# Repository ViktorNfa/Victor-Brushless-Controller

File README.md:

# Victor Brushless Controller (VBC)

This repository contains the **firmware** and **KiCad hardware design files** for the **Victor Brushless Controller (VBC)**, a custom BLDC motor controller inspired by the [Dagor Brushless Controller](https://github.com/byDagor/Dagor-Brushless-Controller).

## Overview

VBC is a compact, ESP32-based brushless controller designed for use in robotic and actuator applications. It integrates key hardware components to support precise control of brushless motors with wired or wireless communication.

The controller supports three operation modes:
- **Position control**.
- **Velocity control**.
- **Torque control**.

In both voltage- and current-control modes. It is compatible with the [SimpleFOC](https://docs.simplefoc.com/) library and can be programmed using the Arduino IDE.

## Features

- ESP32-based microcontroller.
- Onboard 3-phase MOSFET driver and half-bridges.
- Integrated 14-bit magnetic encoder.
- Current sensing resistors.
- Onboard temperature sensor.
- Custom firmware tailored for SimpleFOC.
- KiCad schematics and PCB layout included.

## Hardware Specs

| Specification             | Value           |
|---------------------------|------------------|
| Board Dimensions          | ~44 x 44 mm      |
| Supply Voltage            | 5 – 24 V         |
| Peak RMS Current          | up to 40 A       |
| Magnetic Sensor Resolution| 14 bits          |
| Temperature Range         | -10°C to 120°C   |

> 🧪 Note: This is a **custom derivative project**, still under development. Use with caution and test thoroughly.

## Repository Structure

- `VBC-SW/` – Source code for the controller (Arduino + SimpleFOC).
- `VBC-HW/` – KiCad project files for PCB schematics and layout.
- `KiCad_libraries/` – Custom footprints & symbols needed for KiCad.

## Acknowledgements

Based on the fantastic work by [@byDagor](https://github.com/byDagor) and the [Dagor Brushless Controller](https://docs.dagor.dev/).

## License

To decide – see `...` file for details.

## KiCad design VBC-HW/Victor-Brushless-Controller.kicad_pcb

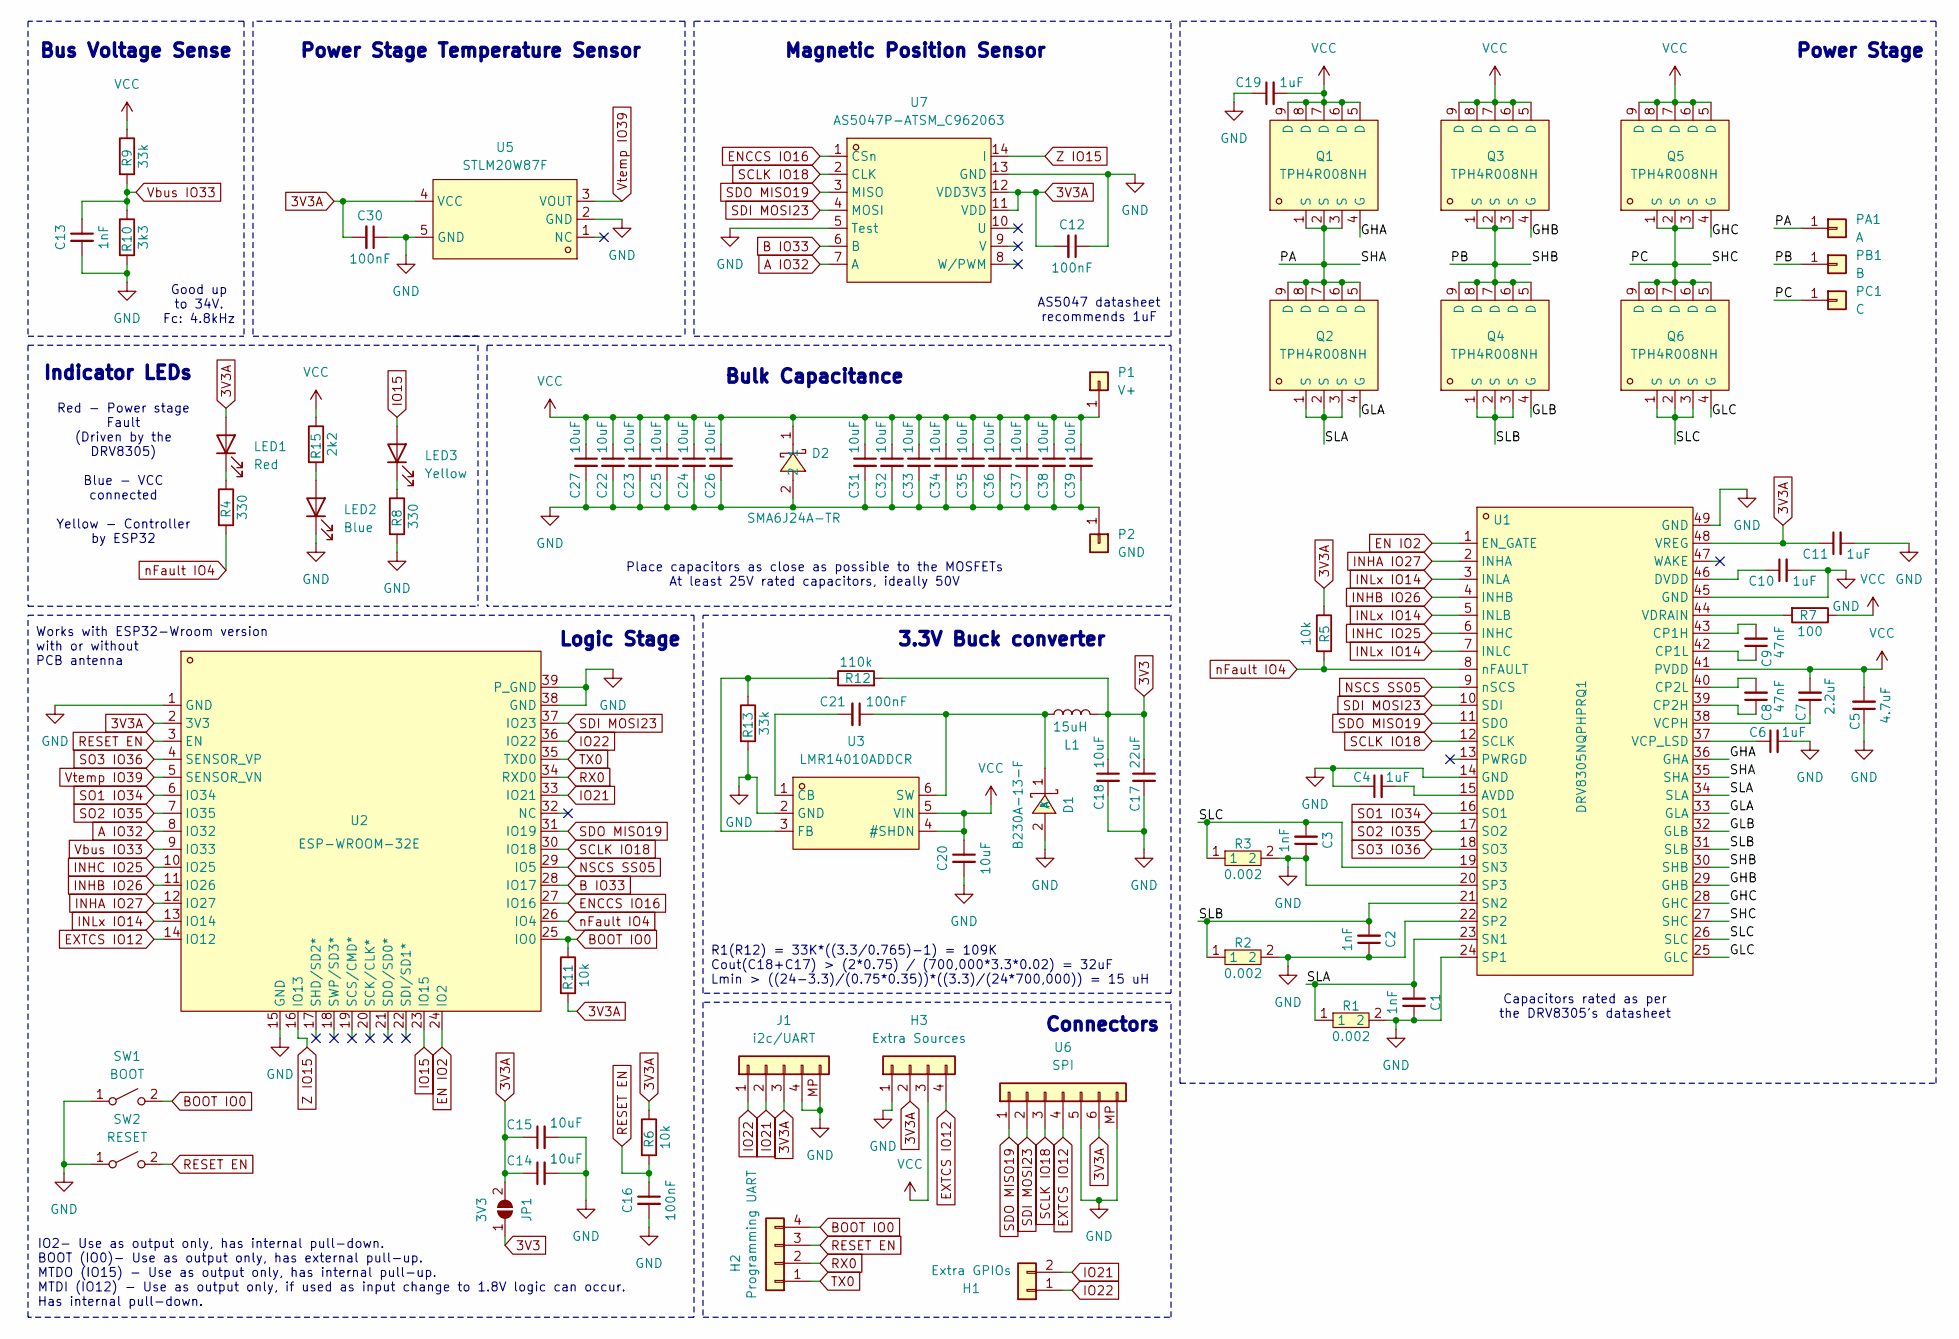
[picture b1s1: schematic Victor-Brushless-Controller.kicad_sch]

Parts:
C1, C2, C3, C13: 1nF; 0402B102K500NT
C4, C6, C10, C11: 1uF; CL05A105KA5NQNC
C5: 4.7uF; 1206B475K500NT
C7: 2.2uF; CL31B225KBHNNNE
C8: 47nF; CL21B473KCFNNNE
C9: 47nF; CL10B473KB8NNNC
C12, C16, C21, C30: 100nF; CL05B104KO5NNNC
C14: 10uF; CL05A106MQ5NUNC
C15: 10uF; CL05B104KO5NNNC
C17: 22uF; CL10A226MQ8NRNC
C18: 10uF; CL10A106MA8NRNC
C19: 1uF; CL10A105KB8NNNC
C20, C22, C23, C24, C25, C26, C27, C31, C32, C33, C34, C35, C36, C39: 10uF; GRM21BR61H106KE43L
C37, C38: 10uF; 1206X106M500NT
D1: B230A-13-F; LCSC Part C12889
D2: SMA6J24A-TR; SMA6J24A; LCSC Part C1975444
H1: Extra GPIOs; PinHeader_1x02_P2.54mm_Vertical
H2: Programming UART; PinHeader_1x04_P2.54mm_Vertical
H3: Extra Sources; PinHeader_1x04_P2.54mm_Vertical
J1: i2c/UART; JST_GH_BM04B-GHS-TBT_1x04-1MP_P1.25mm_Vertical
JP1: 3V3; SolderJumper-2_P1.3mm_Open_Pad1.0x1.5mm
L1: 15uH; PIS3D18P-150M-T
LED1: Red; KT-0603R
LED2: Blue; 19-217
LED3: Yellow; 19-213
P1: V+; Power_Connector
P2: GND; Power_Connector
PA1: A; BLDC_Connector
PB1: B; BLDC_Connector
PC1: C; BLDC_Connector
Q1, Q2, Q3, Q4, Q5, Q6: TPH4R008NH; TPH4R008NH,L1Q(M; LCSC Part C396039
R1, R2, R3: 0.002; CUM2512-24FR002; LCSC Part C323765
R4, R8: 330; 0402WGF3300TCE
R5, R6, R11: 10k; 0402WGF1002TCE
R7: 100; 0402WGF1000TCE
R9, R13: 33k; 0402WGF3302TCE
R10: 3k3; 0402WGF3301TCE
R12: 110k; RC0402FR-07110KL
R15: 2k2; 0402WGF2201TCE
SW1: BOOT; TS342A2P-WZ
SW2: RESET; TS342A2P-WZ
U1: DRV8305NQPHPRQ1; LCSC Part C701780
U2: ESP-WROOM-32E; LCSC Part C19949066
U3: LMR14010ADDCR; LCSC Part C388174
U5: STLM20W87F; LCSC Part C129796
U6: SPI; JST_GH_BM06B-GHS-TBT_1x06-1MP_P1.25mm_Vertical
U7: AS5047P-ATSM_C962063; AS5047P-ATSM; LCSC Part C962063

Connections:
3V3: C17.1, C18.1, JP1.1 (A), L1.2, R12.2
3V3A: C11.1, C12.2, C14.1, C15.1, C30.2, H3.2, J1.3, JP1.2 (B), LED1.2 (A), R5.1, R6.1, R11.2, U1.48 (VREG), U2.2 (3V3), U5.4 (VCC), U6.6, U7.11 (VDD), U7.12 (VDD3V3)
/GHA: Q1.4 (G), U1.36 (GHA)
/GHB: Q3.4 (G), U1.29 (GHB)
/GHC: Q5.4 (G), U1.28 (GHC)
/GLA: Q2.4 (G), U1.33 (GLA)
/GLB: Q4.4 (G), U1.32 (GLB)
/GLC: Q6.4 (G), U1.25 (GLC)
/PA: PA1.1, Q1.1 (S), Q1.2 (S), Q1.3 (S), Q2.5 (D), Q2.6 (D), Q2.7 (D), Q2.8 (D), Q2.9 (D), U1.35 (SHA)
/PB: PB1.1, Q3.1 (S), Q3.2 (S), Q3.3 (S), Q4.5 (D), Q4.6 (D), Q4.7 (D), Q4.8 (D), Q4.9 (D), U1.30 (SHB)
/PC: PC1.1, Q5.1 (S), Q5.2 (S), Q5.3 (S), Q6.5 (D), Q6.6 (D), Q6.7 (D), Q6.8 (D), Q6.9 (D), U1.27 (SHC)
/SLA: C1.2, Q2.1 (S), Q2.2 (S), Q2.3 (S), R1.1, U1.23 (SN1), U1.34 (SLA)
/SLB: C2.2, Q4.1 (S), Q4.2 (S), Q4.3 (S), R2.1, U1.21 (SN2), U1.31 (SLB)
/SLC: C3.2, Q6.1 (S), Q6.2 (S), Q6.3 (S), R3.1, U1.19 (SN3), U1.26 (SLC)
A IO32: U2.8 (IO32), U7.7 (A)
B IO33: U2.28 (IO17), U7.6 (B)
BOOT IO0: H2.4, R11.1, SW1.2 (B), U2.25 (IO0)
EN IO2: U1.1 (EN_GATE), U2.24 (IO2)
ENCCS IO16: U2.27 (IO16), U7.1 (CSn)
EXTCS IO12: H3.4, U2.14 (IO12), U6.4
GND: C1.1, C2.1, C3.1, C4.1, C5.1, C6.2, C10.2, C11.2, C12.1, C13.2, C14.2, C15.2, C16.2, C17.2, C18.2, C19.1, C20.2, C22.2, C23.2, C24.2, C25.2, C26.2, C27.2, C30.1, C31.2, C32.2, C33.2, C34.2, C35.2, C36.2, C37.2, C38.2, C39.2, D1.2 (A), D2.2, H3.1, J1.4, J1.MP, LED2.1 (K), P2.1, R1.2, R2.2, R3.2, R8.2, R10.2, R13.2, SW1.1 (A), SW2.1 (A), U1.14 (GND), U1.20 (SP3), U1.22 (SP2), U1.24 (SP1), U1.45 (GND), U1.49 (GND), U2.1 (GND), U2.15 (GND), U2.38 (GND), U2.39 (P_GND), U3.2 (GND), U5.2 (GND), U5.5 (GND), U6.5, U6.MP, U7.5 (Test), U7.13 (GND)
INHA IO27: U1.2 (INHA), U2.12 (IO27)
INHB IO26: U1.4 (INHB), U2.11 (IO26)
INHC IO25: U1.6 (INHC), U2.10 (IO25)
INLx IO14: U1.3 (INLA), U1.5 (INLB), U1.7 (INLC), U2.13 (IO14)
IO15: LED3.2 (A), U2.23 (IO15)
IO21: H1.2, J1.2, U2.33 (IO21)
IO22: H1.1, J1.1, U2.36 (IO22)
NSCS SS05: U1.9 (nSCS), U2.29 (IO5)
unnamed: C21.1, D1.1 (K), L1.1, U3.6 (SW)
unnamed: LED1.1 (K), R4.1
unnamed: LED2.2 (A), R15.2
unnamed: LED3.1 (K), R8.1
unnamed: C4.2, U1.15 (AVDD)
unnamed: C9.2, U1.43 (CP1H)
unnamed: C9.1, U1.42 (CP1L)
unnamed: C8.1, U1.39 (CP2H)
unnamed: C8.2, U1.40 (CP2L)
unnamed: C10.1, U1.46 (DVDD)
unnamed: C7.1, U1.38 (VCPH)
unnamed: C6.1, U1.37 (VCP_LSD)
unnamed: R7.2, U1.44 (VDRAIN)
unnamed: C21.2, U3.1 (CB)
unnamed: R12.1, R13.1, U3.3 (FB)
RESET EN: C16.1, H2.3, R6.2, SW2.2 (B), U2.3 (EN)
RX0: H2.2, U2.34 (RXD0)
SCLK IO18: U1.12 (SCLK), U2.30 (IO18), U6.3, U7.2 (CLK)
SDI MOSI23: U1.10 (SDI), U2.37 (IO23), U6.2, U7.4 (MOSI)
SDO MISO19: U1.11 (SDO), U2.31 (IO19), U6.1, U7.3 (MISO)
SO1 IO34: U1.16 (SO1), U2.6 (IO34)
SO2 IO35: U1.17 (SO2), U2.7 (IO35)
SO3 IO36: U1.18 (SO3), U2.4 (SENSOR_VP)
TX0: H2.1, U2.35 (TXD0)
VCC: C5.2, C7.2, C19.2, C20.1, C22.1, C23.1, C24.1, C25.1, C26.1, C27.1, C31.1, C32.1, C33.1, C34.1, C35.1, C36.1, C37.1, C38.1, C39.1, D2.1, H3.3, P1.1, Q1.5 (D), Q1.6 (D), Q1.7 (D), Q1.8 (D), Q1.9 (D), Q3.5 (D), Q3.6 (D), Q3.7 (D), Q3.8 (D), Q3.9 (D), Q5.5 (D), Q5.6 (D), Q5.7 (D), Q5.8 (D), Q5.9 (D), R7.1, R9.1, R15.1, U1.41 (PVDD), U3.4 (#SHDN), U3.5 (VIN)
Vbus IO33: C13.1, R9.2, R10.1, U2.9 (IO33)
Vtemp IO39: U2.5 (SENSOR_VN), U5.3 (VOUT)
Z IO15: U2.16 (IO13), U7.14 (I)
nFault IO4: R4.2, R5.2, U1.8 (nFAULT), U2.26 (IO4)

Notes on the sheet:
3.3V Buck converter
Red - Power stage Fault (Driven by the DRV8305) Blue - VCC connected Yellow - Controller by ESP32
Power Stage Temperature Sensor
Capacitors rated as per the DRV8305's datasheet
Indicator LEDs
Power Stage
AS5047 datasheet recommends 1uF
Place capacitors as close as possible to the MOSFETs At least 25V rated capacitors, ideally 50V
Works with ESP32-Wroom version with or without PCB antenna
Bus Voltage Sense
Good up to 34V. Fc: 4.8kHz
Bulk Capacitance
Connectors
Magnetic Position Sensor
R1(R12) = 33K*((3.3/0.765)-1) = 109K Cout(C18+C17) > (2*0.75) / (700,000*3.3*0.02) = 32uF Lmin > ((24-3.3)/(0.75*0.35))*((3.3)/(24*700,000)) = 15 uH
IO2- Use as output only, has internal pull-down. BOOT (IO0)- Use as output only, has external pull-up. MTDO (IO15) - Use as output only, has internal pull-up. MTDI (IO12) - Use as output only, if used as input change to 1.8V logic can occur. Has internal pull-down.
Logic Stage

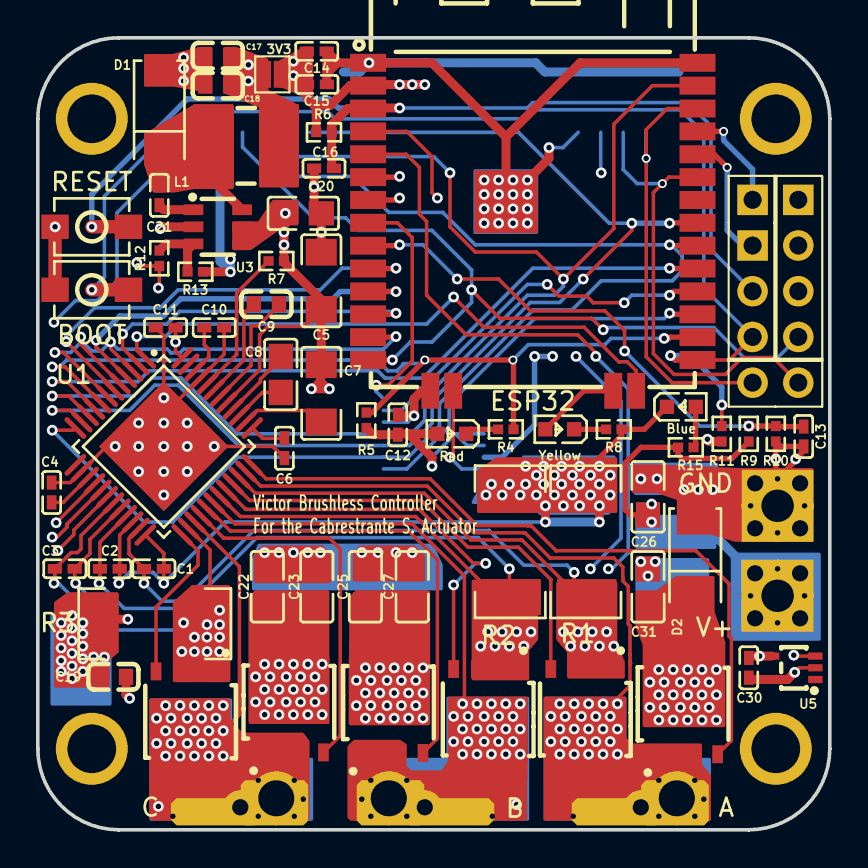
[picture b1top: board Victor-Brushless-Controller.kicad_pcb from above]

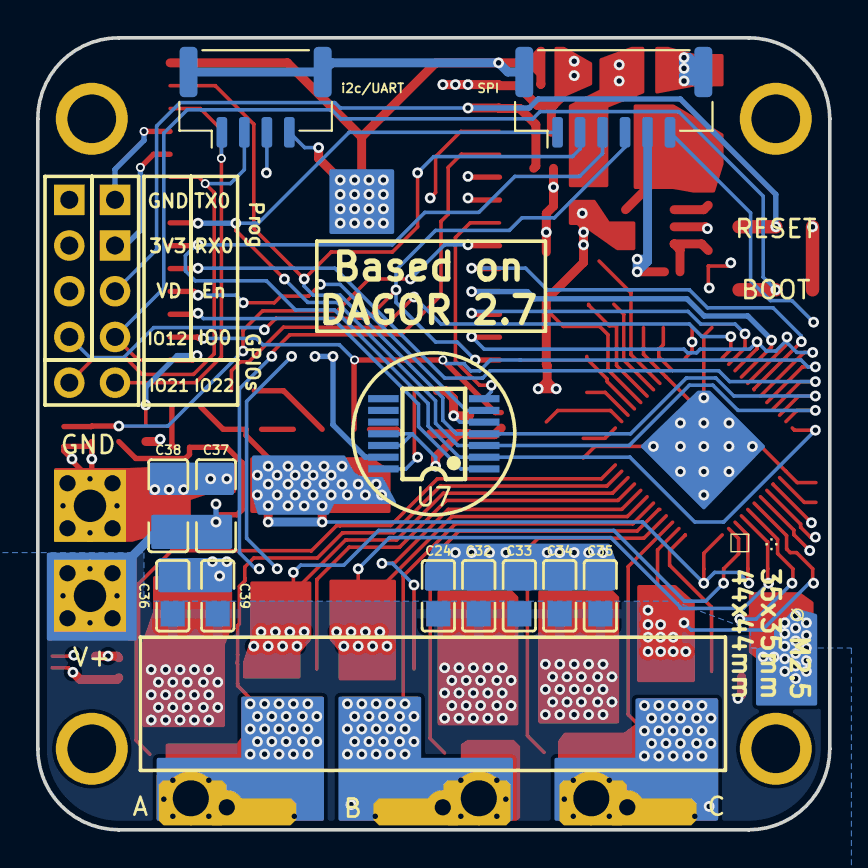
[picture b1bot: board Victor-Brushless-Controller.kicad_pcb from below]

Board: 4 copper layers, 44.0 x 44.0 mm, 81 parts (13 on the bottom side), 58 nets.

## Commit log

2025-03-29 Added KiCad libraries
2025-03-30 Added more micros and LCSC numbers
2025-04-01 Finished Power Stage schematic
2025-05-23 Added Kicad schematic magnetic, bus and temp
2025-05-26 Added buck converter
2025-05-26 Finished schematics connections
2025-05-26 Cleaned up schematic
2025-05-27 Started adding footprints
2025-06-02 Updated more components
2025-06-02 Fix errors
2025-06-03 Finish adding all components libraries
2025-06-03 Added footprints to project
2025-06-05 Added footprints to schematic
2025-06-12 Assigned external connectors
2025-06-12 Finished assigning and creating all footprints
2025-06-12 Ready to tetris
2025-06-14 Preliminary component placing
2025-06-14 PCB starting to take shape
2025-06-21 Updated PCB and code
2025-06-21 Added test codes for magnetic sensor
2025-06-21 Added dev branch of simpleFOC lib
2025-06-23 Adding new base tests
2025-06-24 Working with smaller GM3506 motor
2025-06-25 Updates connections in board
2025-06-25 Managed to get Getting started codes to work
2025-07-10 Added closed loop control
2025-07-11 Fix closed loop control
2025-07-12 Added init current sense
2025-07-14 Added current closed loop control test
2025-07-14 Fix current control
2025-07-16 Fixed basic current sense
2025-07-16 foc_current control now works
2025-07-16 Added infor about phase order
2025-07-18 Cleaned up the codes to work with Dagor version
2025-07-18 Working clean up of current control
2025-07-19 Final final cleanups
2025-07-19 Added tests for LA8308 motor
2025-07-20 Big motor working
2025-07-22 Tuned LA8308
2025-07-28 Added code for whacakapuncher
2025-07-29 Added temperature sensor
2025-07-30 Might be wrong, just saving for history
2025-07-30 Revert "Might be wrong, just saving for history"
    This reverts commit cdf17d161a2acca385215cf7318953e3e6c9fc40.
2025-07-30 Save scumming
2025-07-30 Final save for bar torque setup
2025-08-10 Starting added traces to board
2025-08-11 Finished top layer connections
2025-08-13 Finished vias and Inner layer 1
2025-08-14 Started finishing vias conencting in top later
2025-08-15 Finished all connections
2025-08-15 Fully finished board
2025-08-15 Got 3D model
2025-08-20 Cleaned up some code
2025-08-20 Created safe version
2025-08-22 Cleanup some code for basic version of big motor no load
2025-08-22 Final runed version of big motor
2025-08-24 espnow works!
2026-01-05 Added cody ready for fatigue test of actuator
2026-01-11 Fix code issues for Alvi test
